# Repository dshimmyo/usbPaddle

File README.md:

I'm pretty nostalgic about old game consoles like the Atari 2600, and for years I've been wondering why I can't play games like Breakout or Kaboom! or Warlords with a proper paddle controller, so I set out to find out what I can do about it.
This project is the beginning of that adventure.
Basically, this is some arduino code that I installed into an Adafruit Keeboar 2040 which is based on and RP2040. Some time in the near future I'll build a more generic version using the RP2040.
Anyway, the gist of it is, you'll need a 10K potentiometer with ground on one outer lug and 3.3vdc on the other outer lug. The wiper is wired to one of the analog input pins on the kb2040.
The analog signal you get from the potentiometer is your paddle rotation. It's all in the code.
The reason this script is so huge is because I had to experiment with a bunch of modes to see what works where. But basically, just use the default mode.
Unfortunately it only works on basically on or two devices using one specific OS. I got it working on an Anbernic RG350xxH and RG40xxH running MuOS Banana.
For some reason, using that specific OS and whatever version of retroarch they use, it works great with the paddle. Every other software, OS compbination I've tried maps the paddle as if it's a joystick so it control velocity which is wrong.
The paddle is supposed to map directly to the position of the paddle.

Anyway, this would make more sense in a video and I'll post a schematic of my circuit soon.

Oh I forgot to mention I had to add a bunch of buttons to this paddle because when I switch to this device in retroarch I can't use the buttons on the anbernic so I needed a way to navigate out of the retroarch menus to play the game, thus all the dang buttons.

In this image I'm running a gametank game using the GameTankEmulator which has native support for my paddle because I programmed it that way ;)

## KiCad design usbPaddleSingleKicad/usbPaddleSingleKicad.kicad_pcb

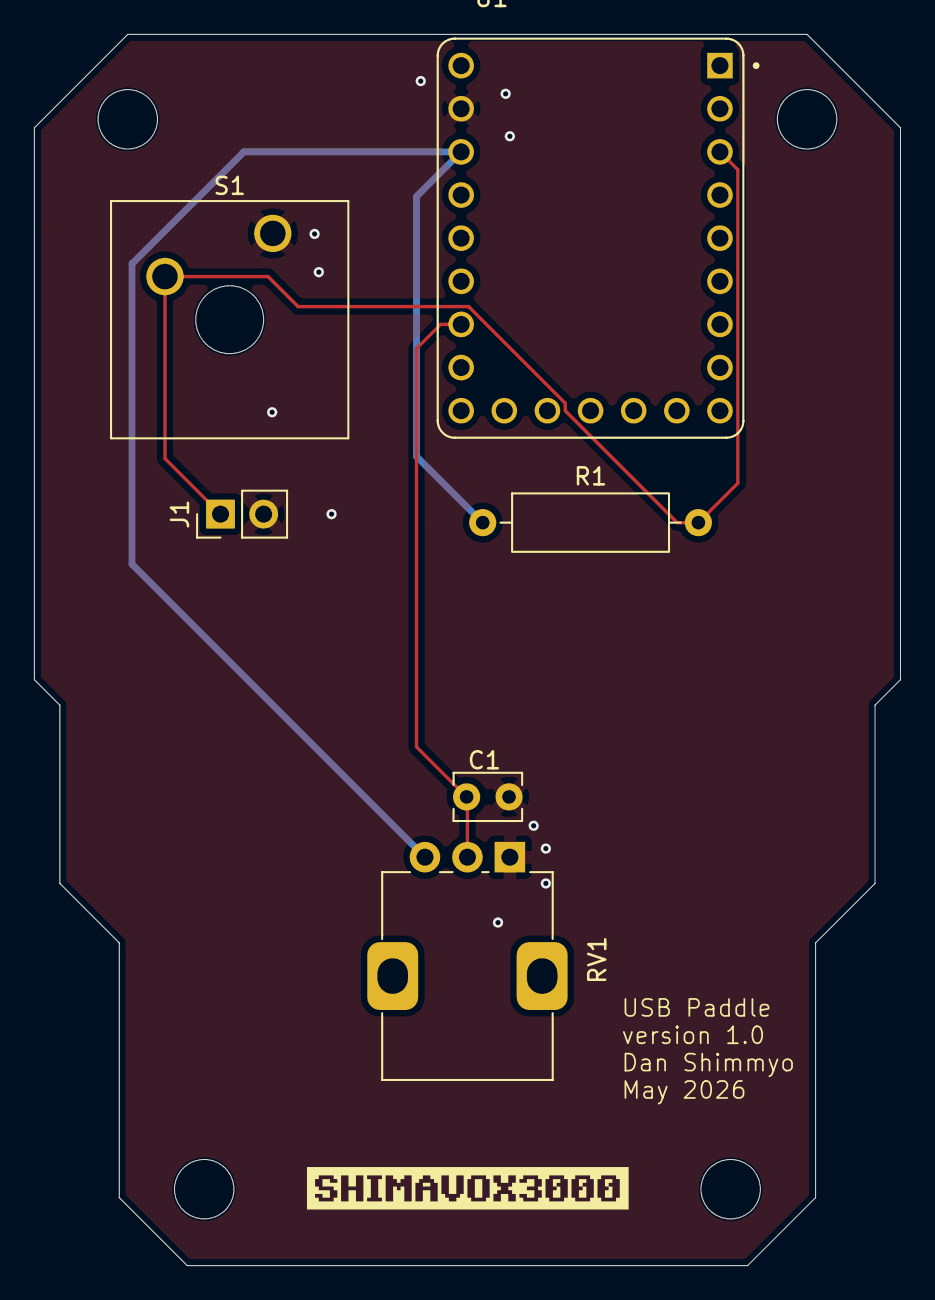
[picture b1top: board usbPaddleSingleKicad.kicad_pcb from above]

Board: 2 copper layers, 51.0 x 72.5 mm, 6 parts (0 on the bottom side), 4 nets.

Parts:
C1: .1µF; C_Disc_D3.8mm_W2.6mm_P2.50mm
J1: Conn_01x02_Pin; PinHeader_1x02_P2.54mm_Vertical
R1: 10kΩ; R_Axial_DIN0309_L9.0mm_D3.2mm_P12.70mm_Horizontal
RV1: R_Potentiometer; Potentiometer_Alps_RK09K_Single_Vertical
S1: SW_Cherry_MX_1.00u_Plate
U1: RP2040-ZERO; MODULE_RP2040-ZERO

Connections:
GND: C1.1, J1.2, RV1.1, S1.1, U1.22 (GND)
unnamed: J1.1, R1.2, S1.2, U1.3 (GP2)
unnamed: C1.2, RV1.2, U1.17 (GP26)
VCC: R1.1, RV1.3, U1.21 (3V3)

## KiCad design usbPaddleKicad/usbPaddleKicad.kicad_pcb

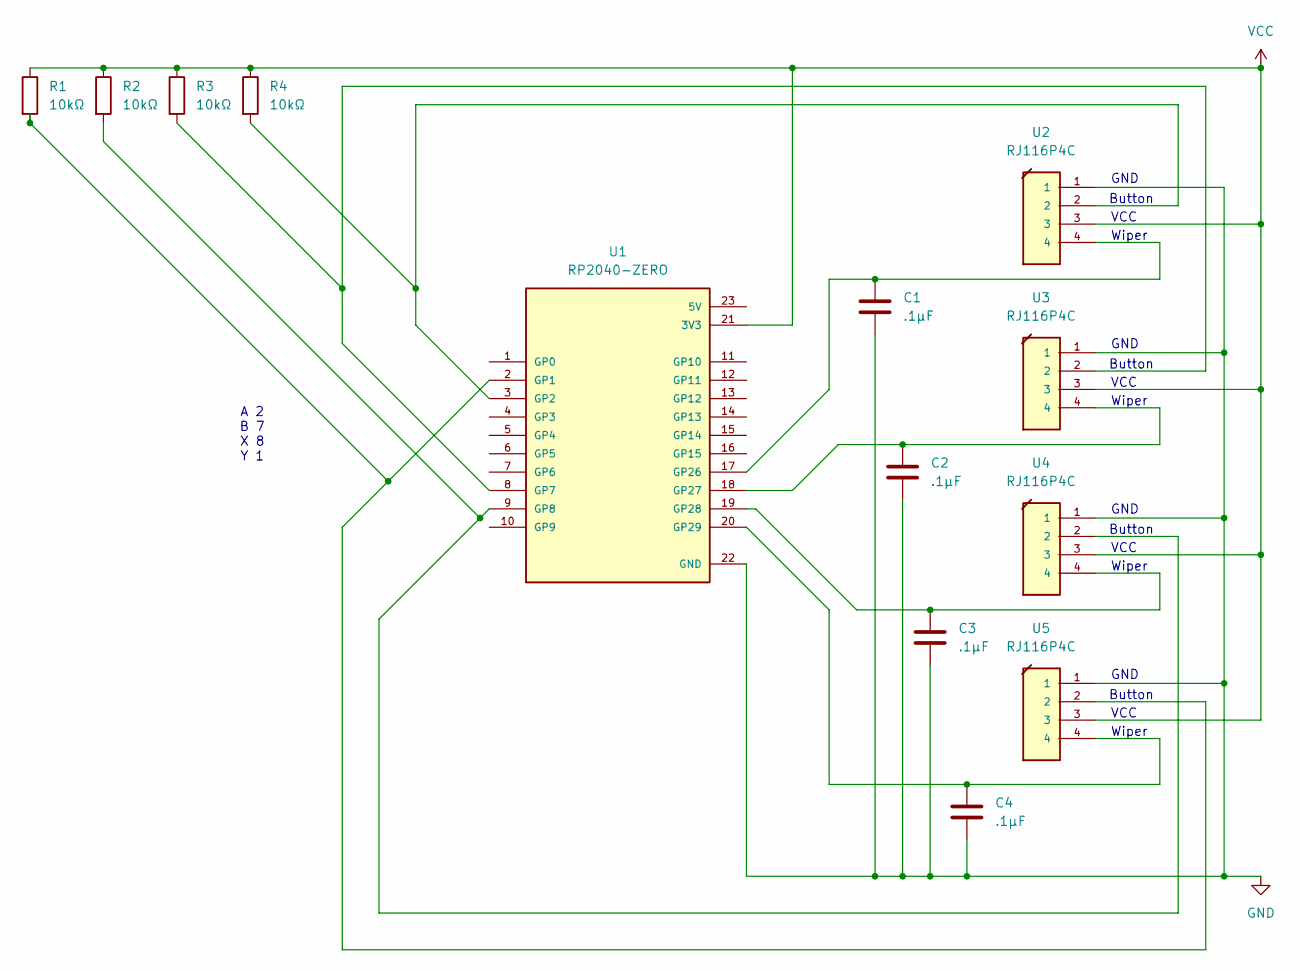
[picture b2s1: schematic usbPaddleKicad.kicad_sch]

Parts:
C1, C2, C3, C4: .1µF; C_Disc_D3.8mm_W2.6mm_P2.50mm
R1, R2, R3, R4: 10kΩ; R_Axial_DIN0309_L9.0mm_D3.2mm_P12.70mm_Horizontal
U1: RP2040-ZERO; MODULE_RP2040-ZERO; PARTREV NA
U2, U3, U4, U5: RJ116P4C; RJ6P4C_GLX-N-64M

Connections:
GND: C1.1, C2.1, C3.1, C4.1, U1.22 (GND), U2.1, U3.1, U4.1, U5.1
unnamed: R1.2, U1.2 (GP1), U5.2
unnamed: R4.2, U1.3 (GP2), U2.2
unnamed: R3.2, U1.8 (GP7), U3.2
unnamed: R2.2, U1.9 (GP8), U4.2
unnamed: C1.2, U1.17 (GP26), U2.4
unnamed: C2.2, U1.18 (GP27), U3.4
unnamed: C3.2, U1.19 (GP28), U4.4
unnamed: C4.2, U1.20 (GP29), U5.4
VCC: R1.1, R2.1, R3.1, R4.1, U1.21 (3V3), U2.3, U3.3, U4.3, U5.3

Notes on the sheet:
VCC
Wiper
GND
Button
A 2 B 7 X 8 Y 1

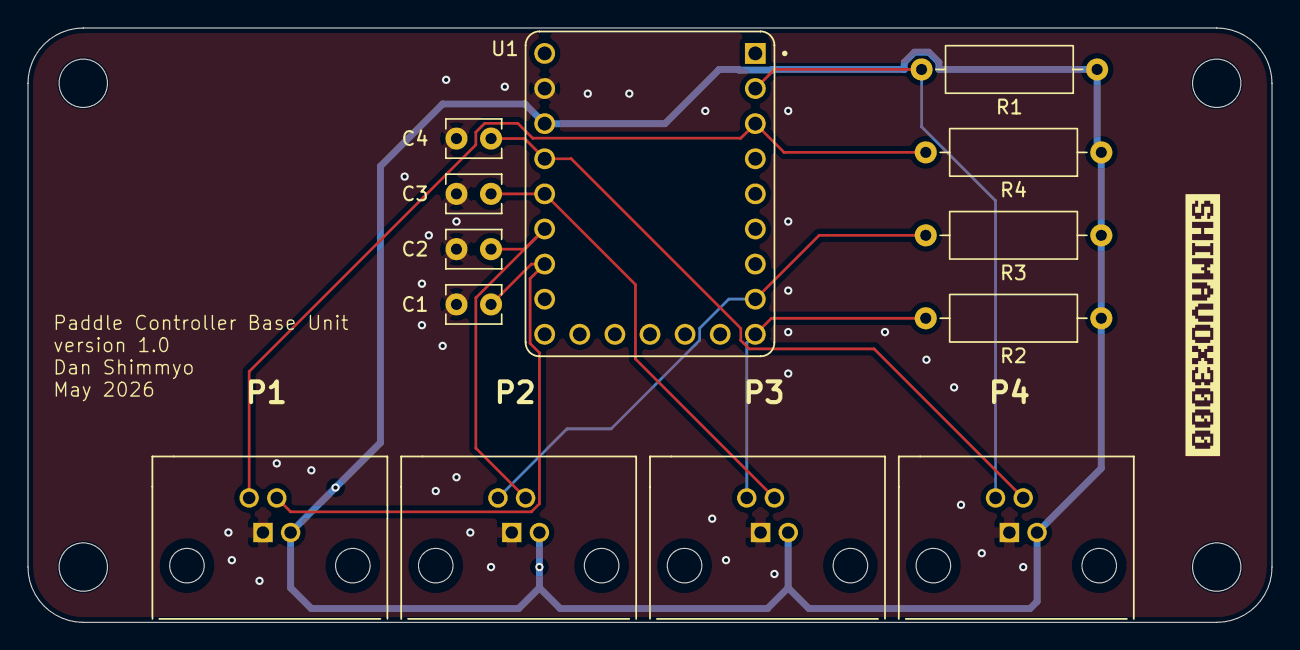
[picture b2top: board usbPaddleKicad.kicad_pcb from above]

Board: 2 copper layers, 90.0 x 43.0 mm, 13 parts (0 on the bottom side), 10 nets.

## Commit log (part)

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2026-04-19 add start and select
2026-04-19 works in retroarch now
2026-04-19 add rumble support
2026-04-19 spoofing works but rumble fails
2026-04-19 attempt to make rumble more accessible but no difference
2026-04-20 hardware tester likes it but it doesn't work on anbernic/retroarch
2026-04-20 control that initial rumble test
2026-04-20 adding 3 new buttons and flip/flop a and b buttons
2026-04-20 anbernic / retroarch mappings
2026-04-21 pin assignments for 4 paddle hub
2026-04-23 manually defining hid_report to try to add steamdeck without breaking anbernic/retroarch
2026-04-23 comments
2026-04-27 clean out messy comments
2026-04-27 beginning setup, but looks too limited
2026-04-27 remove another comment
2026-04-27 add toggle for ps4 and xinput spoofing, untested
2026-04-28 add mouse mode for steamdeck (doesn't work)
2026-04-28 mouse descriptor that seems to work
2026-04-28 removed experimental untested steam deck hack in normal mode
2026-04-30 Initial README.md with project overview and setup
    Added project description and details about paddle controller setup.
2026-04-30 Add MIT License
    Added the MIT License to the project.
2026-05-04 changed credentials
2026-05-04 adds internal pull-down to adc pins attempt to center pot when disconnected but it doesn't work. The circuit probably need a pull-down resistor
2026-05-04 simple single profile, cleaned up
2026-05-04 changed orientation of face buttons to match xbox standard, easier to do it here rather than on my prototype
2026-05-04 rearranged face button pins to match my hacky perfboard physical layout
2026-05-04 switch to x-box standard button profile for maximum compatibility
2026-05-04 fill out unused buttons for max compatibility
2026-05-04 add support for 4 paddles
2026-05-15 add kicad project
2026-05-15 wired 4 jacks to rp2040 in schematic
2026-05-15 added filter caps and pull-up resistors
2026-05-15 pcb layout first pass, not fully routed
2026-05-15 clean up pcb edges and corners
2026-05-15 add silkscreens
2026-05-16 added port numbers
2026-05-16 port numbering in back silkscreen
2026-05-17 gerbers
2026-05-17 final gerbers
2026-05-18 update RJ11 port footprints from library
2026-05-20 Changed descriptor from gamepad to joystick
2026-05-20 name change
2026-05-22 add new project for usb single paddle basic schematic done
2026-05-22 new single paddle pcb
2026-05-23 adjust layout
2026-05-23 single paddle gerbers
2026-05-24 add step and stl models
2026-06-07 changed 4th player paddle axis to axis 3
